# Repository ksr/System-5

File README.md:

# System-5 — a PCB-based 1802 ELF

System-5 is a printed-circuit-board 1802 computer built in 2004–2005 to run
Mike Riley's **ELF/OS**. It replaced the wire-wrapped System-4 (1979–1982) one
card at a time while keeping the System-4 30-pin bus, so old wire-wrap cards and
new PCB cards could be mixed. All the 2005 boards were designed in **Eagle 4.x**;
the boards of 2026 are **KiCad** designs.

Original write-up: the 2005 1802 website, no longer online; a copy is in `docs/website-2005/`.

The project's website is <https://system5.cottageworker.com>. This repository is public as
<https://github.com/ksr/System-5>, a copy made from Ken's working repository (`tools/public/README.md`).

## The system

| Card | Folder | Summary |
|---|---|---|
| Bus | `hardware/bus` | The 30-pin bus kept from System-4: Rev A 1982, Rev B Dec 2005 (dropped ±12V, added N1/N2); pinout in `hardware/board-notes/BoardNotes.txt`. **In the machine: the 2009 PCB backplane**, six 36-pin slots, no regulator, no pull-ups (System-4's backplane was Vero board). **Rev D** (S5BUS-D, 2026, `kicad/rev-d/`): eight 36-pin slots, power switch, fuse, pull-ups and pull-downs. Designed, not ordered. |
| CPU | `hardware/cpu` | CDP1802, clock, CM1232 power-on reset/auto-run, mode control (run/load/wait/reset), 4K EPROM, VMA reset-address remap, EF jumpers, aux connectors for the front panel and 1861 card. **In the machine: Rev A** (Jan 2005, reworked). Rev B/C are unbuilt fixes; `eagle/cpu1-prototype` = first unrouted cut with the 1861 on board. **Rev D** (2026, `kicad/rev-d/`): a new CPU card for the 36-pin bus, 2 MHz or an external clock, RESET/RUN switch, a flag that lets a loaded program run from RAM after a reset, with a RAM LED to show it (2026-11-21). Designed, not ordered. |
| Memory | `hardware/memory` | 2× 62256 RAM + 2× 27256 EPROM, every 4K block jumper-enabled. **In the machine: Rev E** (MEM3-E, `kicad/rev-e/`; JLCPCB, 4 layers, built 2026-10-31): the 2005 Rev C circuit with three fixes. Before it: Rev A (2004, the first card built) → B (2005; reworked, in the machine until 2026) → C, and a 2014 `rev-c-mill` variant for PCB milling. Rev D (2026) is scrap. `mem1`/`mem2` are earlier 6116-based designs. |
| IO: 1861 video + keyboard | `hardware/io-1861-keyboard` | CDP1861 video, CDP1852 input port, I/O decode (from Mike Riley's ELF). PS/2 keyboard → **PAK-VI** (AWC Electronics PS/2-to-ASCII) → **PIC16F84** (serial→parallel, `pic-ps2-firmware/keyboard.c`) → 1852. **In the machine: Rev A** (Jan 2005), for the keyboard; the 1861 has never been tested. |
| 6845 video | `hardware/video-6845` | 6845 alphanumeric video card based on **BYTE, May 1979**. Composite + Electrohome drive outputs. Rev A Feb 2005 (the first working card, later stripped; `eagle/rev-a/`). **In the machine: Rev B** (lower case, simplified clocking, Apr 2005): the 2005 Eagle source in `eagle/rev-b/` and the KiCad order master in `kicad/rev-b/`. **Rev B-Clean** (2026, `kicad/rev-b-clean/`): Rev B's circuit and copper without the DE-9 (composite only) and with the 6845's light-pen input tied to ground, every part drawn and the silkscreen redone. Designed, not ordered. **Rev B-Clean-Keyboard** (2026, `kicad/rev-b-clean-keyboard/`): Rev B-Clean with a PS/2 keyboard on the card (VIDEO-G TEXT's keyboard section: the key at 7802, the status at 7804), the 36-pin bus connector, and the video and keyboard jacks together at the front edge; it runs the VIDEO-G HBIOS. Designed, not ordered. |
| CF disk (IDE) | `hardware/ide-cf` | Mike Riley's 8-bit IDE interface plus port-select jumpers; used with a CF-to-IDE adapter and a 16MB CF card. **In the machine: Rev A** (Feb 2005). |
| Breadboard proto | `hardware/proto-breadboard` | Solderless-breadboard prototyping card. Drawn in 2005, never made. |
| Bus driver | `hardware/bus-driver` | New, 2026: Arduino Nano and 2× MCP23017 on the bus, a test card after the YACC1 bus tester. It runs bus cycles in place of the CPU, or steps and traces the CPU. **Rev B** (BUSDRV-B, `kicad/rev-b/`; JLCPCB, 2 layers) is built and working since 2026-10-30. Rev A is scrap: routed on 4 layers, ordered from a 2-layer zip. **Rev C** (BUSDRV-C, `kicad/rev-c/`, drawn 2026-11-18, not ordered): all 36 bus positions with a third MCP23017, LOAD mode by the clock, CLK OUT and probes on the Nano, a DEBUG header cabled to CPU Rev D's. The firmware has a **short finder** for either card since 2026-11-21: one bus line driven alone, every other watched (`python3 bringup.py shorts`, `software/busdrv/BRINGUP.md`); tried in the simulator only. |
| IO panel | `hardware/io-panel` | New, 2026: the front panel as a card on the 36-pin bus. 8 toggles, 8 LEDs, six TIL311 hex displays (the data byte and the bus address), Q LED, INPUT button, ELF-style RUN/LOAD, a real-time clock and, since 2026-11-20, a serial port (16C550, DE-9). Since 2026-11-22 a 50-pin header at its front edge for the front panel's ribbon (the card is 8.00 in long), and its DMA request put right: as first drawn it would have loaded every byte twice. Since 2026-11-23 its own RESET button, which boots the EPROM (the RUN/RESET toggle restarts what ran before), and the serial port's settings on the silkscreen. Since 2026-11-25 its DMA request and the toggles' drive start from a known state at power-up (D1, R5, R6; U23 a 74HCT03), and since 2026-11-26 its RESET button is at the far end of the front edge from INPUT. Rev A (`kicad/rev-a/`) designed, not ordered. No front panel was designed in 2005: the System-4 wire-wrap panel was used via the CPU card header. |
| Front panel | `hardware/front-panel` | New, 2026-11-22: a board that mounts as the front of a case, on a 50-way ribbon from the IO panel card. Six TIL311s (the bus address and the data byte), bit and status LEDs (PWR, Q, PAUSE, RESET, ROM, START FROM RAM), eight data toggles, RUN and LOAD, INPUT, and a RESET button that boots the EPROM (beside START FROM RAM since 2026-11-26, away from INPUT). Nothing goes to the CPU card: a boot reset is a state of the bus (`docs/manual/bus.md`). Rev A (`kicad/rev-a/`) designed, not ordered. |
| VIDEO-G | `hardware/video-g` | New, 2026: the next video card, two boards joined by a 40-pin ribbon. **TEXT**: 6845 text, 64 × 25 or 64 × 32, with a PS/2 keyboard. **GFX**: graphics, 512 × 200 or 512 × 256, with a PS/2 mouse. All memory-mapped in its own block, no I/O ports (2026-11-17). Version 1.0 (`kicad/`) designed, not ordered. |

The machine today (2026-11-14) is the 2009 backplane with CPU Rev A, memory Rev E, 6845 Rev B, IO Rev A and IDE Rev A. The five new boards (bus Rev D, CPU Rev D, the IO panel and the two VIDEO-G boards) pass the older check, `tools/preorder_check.py`, and none is ordered. Before an order each has to pass `pcb-check`, Ken's check for the boards of all his systems since 2026-11-06 (`hardware/BUILD-RULES.md`, section 2): all five have, as they are now: the bus Rev D on 2026-11-18, the other four on 2026-11-19, after their labels were moved out from under the bus connector (and VIDEO-G TEXT got the 36-pin connector); the IO panel again on 2026-11-20, with its serial port; CPU Rev D again on 2026-11-21, with its RAM LED. On 2026-11-22 CPU Rev D and the IO panel were changed and a sixth board, the front panel, was drawn (a boot reset on the bus; the IO panel's header and its DMA request): all three pass `pcb-check --tests` (last on 2026-11-23, at `26e17ea`: CPU Rev D and the front panel with no failures and no warnings, the IO panel with no failures and one warning, which Ken accepted that day: its DE-9 begins 65.6 mm from the front edge, where the check allows 60). They were drawn on the branch `front-panel` and are in `main` since 2026-11-23 (Ken: "merge everything"). Since then: VIDEO-G TEXT routed again with its 6845 write-only (2026-11-24; `pcb-check --tests` at `38fc4d0`, no failures, 0 warnings, GFX the same), the IO panel's power-up fix (2026-11-25), and both panels' RESET buttons moved away from INPUT (2026-11-26; `pcb-check --tests`: the front panel at `803c3a8`, no failures, 0 warnings; the IO panel at `6f4359d`, no failures, the accepted warning). None is ordered. `STATUS.md` has every board's state.

Board conventions (size 5.50" × 3.75", LED positions, labelling `KSR -- XXX#-A`,
CAM jobs) are in `hardware/board-notes/`.

Each board has an `eagle/<rev>/` tree (production gerbers in `fab/`) and, once converted, a `kicad/<rev>/` tree. Which boards were ordered: `hardware/FABRICATED.md`. Open work: `BACKLOG.md`. A summary of where everything stands (2026-11-14): `STATUS.md`.

Where both the Eagle working folder and the published website had a file with
the same name but different content, the website version is kept in a
`website-copy/` subfolder. Eagle's numbered backups (`*.b#1`, `*.s##`, …) are in
`eagle-backups/` subfolders.

## Firmware (Ken's)

- `firmware/hbios/` — **HBIOS**: 6845 video and keyboard drivers layered on Mike
  Riley's ELF/OS BIOS (changes marked `#define KSR`); boots into the BIOS's
  monitor, `minimon`, which is Mike's. `v1.0.6` is current, in the machine since 2026-11-15 (v1.0.4 plus the commands
  Ken added to that monitor, `H`, `B`, `D` and `Q1` / `Q0`, and the disk calls
  always in LBA mode, which Elf/OS v5 needs; built by its `build.py`); `v1.0.5`, `v1.0.4`, `v0.9` and `old/` are
  earlier builds. `v1.0.7` (2026-11-17, burned that day, not yet in the machine) adds `@F1E0`: the code of each key pressed, as `0x31`, on the
  bottom line of the screen, until Reset. `v1.0.8` (2026-11-18, emulator only) adds a driver for the IO panel's real-time
  clock (a DS12885 on ports 6/7) behind `f_gettod` / `f_settod`, and `f_getdev` bit 4. v1.0.4 builds with `rcasm` + `srec_cat` into a ROM
  at `0xF000`. `video-g/` is a build for the VIDEO-G card (everything
  memory-mapped: the 6845 at 7800/7801, the key at 7802; 64 x 25, a faster scroll; for the emulator, not burned).
  Mike Riley's BIOS comes under his notice (`firmware/hbios/NOTICE.md`: free to use and share with the notice kept,
  not for commercial use without his permission).
- `firmware/rom-tests/` — test ROM (`sec2`).
- `firmware/char-rom-fonts/` — 2513 character-generator ROM images and C tools
  to build/view font EPROMs for the 6845 card.

## Software (Ken's host tools)

- `software/s5emu/` — System-5 emulator and debugger (terminal + browser; in a browser tab on a Mac or in a GitHub Codespace: `software/s5emu/CODESPACE.md`, `.devcontainer/`): runs the real HBIOS ROM and boots ELF/OS from a disk image; 1861, IDE/CF, 6845, keyboard, memory jumpers, bus-driver link; `--video g` models the VIDEO-G card.

- `software/gbasic/` — **GBASIC**, an integer BASIC for ELF/OS with VIDEO-G graphics (1802 assembly, 2026-11-01): the source, the built program, its language reference (`README.md`) and tests in the emulator.

- `tools/render_populated.py` — a KiCad render of a board with its parts drawn in, for the website's pictures (the board file is only read)
- `tools/asm1802.py` — a Python 1802 assembler (rcasm syntax, short-branch page check, relaxing jumps, macros); builds GBASIC and the VIDEO-G HBIOS.

- `software/busdrv/` — `s5busdrv.py`, the host tool for the bus driver card (peek/poke/dump, hex load with verify, memtest, I/O, bus watch); firmware in `embedded/bus-driver/`.

- `software/elfos-v5/` — System-5 programs for Mike Riley's Elf/OS v5 (`cls`) and `v5card.py`, which reads and
  changes a v5 card image (`ls`, `get`, `put`, `add`).

## Kept private (third-party)

Other people's work that System-5 is built with, and that carries no permission to publish it, is not in this
repository. Since 2026-11-15 it is in Ken's private repository `private-resources` (`github.com/ksr/private-resources`),
which sits beside this one, so the paths below are written `../private-resources/elf/...`; each keeps the path it had
here.

- `reference/mike-riley/` — **ELF/OS** (kernel 135, utilities and languages,
  0.2.6 release; Elf/OS v5 and its System-5 card image), **rcasm** 2007 source, **EDTASM**, MicroElf/PicoElf boards
  and a mirror of elf-emulation.com.
- `reference/elf2000-spare-time-gizmos/` — **ELF2000** (Spare Time Gizmos /
  Bob Armstrong): manuals, EELF, ELF-Disk, STG1861, ROM v60/v87 images (with
  Ken's EPROM-split Makefiles), ElfOS-2K 0.2.8. Not part of System-5.
- `reference/tiny-basic/` — Lee Hart/TMSI 1802 Tiny BASIC; RCA Tiny BASIC (Herb Johnson).
- `reference/tools/` — A18 assembler, TASM 3.1, 1806 disassembler, srecord
  source tarballs (1.20/1.23/1.27), Macro Assembler AS manual, LCD font tool.
- `reference/datasheets/` — CDP1802 datasheet, RCA MPM-201A 1802 User Manual (1976), EPROM databook.
- `firmware/elfos-install-rom/` — the ELF/OS install image for the memory card's EPROM, and the read of the one in
  MEM3-E's IC5 (`hardware/memory/eagle/rev-b/bringup/*.bin`).
- `firmware/system4-tiny-basic-rom/` — the Tiny BASIC EPROM pulled from the System-4 wire-wrap machine, and its
  disassembly.
- `software/disktool/` — Mike Riley's 2005 disktool, which builds and writes ELF/OS disks (with `kernel.bin`).
- `software/rcasm-mac-build/` — rcasm source patched in 2017 to build on macOS (with a Mac x86_64 binary).

Without them the emulator still runs HBIOS (whose BIOS part Mike Riley allows to be shared, above), but has no ELF/OS
disk to boot, and the tests that need one are skipped.

## Licence

Ken's designs and documents are CC BY 4.0, his software MIT; HBIOS's BIOS part, the 2513 fonts and some library parts
are other people's: [`LICENSE.md`](LICENSE.md).

## Docs

- `docs/website-2005/` — "Ken's 1802 World" site (System-1, System-4, System-5,
  stand-alone projects, photos). Files that are also elsewhere in this repo
  (schematics, BIOS source, tool tarballs) were removed here (the list is
  `docs/.removed-dups.txt`, kept with Ken's working notes).
- `docs/website-older/` — earlier versions of the same site.

The visitor counter the Yahoo host added to 33 of the old pages was taken out on 2026-11-15; nothing else in them was
changed.

## Other projects

1802 work that is not System-5 (the Netronics ELF II recreation, the 2020 COSMAC ELF PCB, the ELF2000/PicoElf
ROMs, the ET-3400 EPROM reads and general 1802 documentation) is in a separate private repository since 2026-10-26,
split out of this one with its history.

## Provenance

Assembled 2026-10-04 from `~/Documents/Projects/elf-1`, `elf-2` and `1802`
(all left untouched). `elf-1` was largely a subset of `elf-2`; exact duplicates were
collapsed to one copy. Not carried over: FrontPage `_vti_*` metadata, vim swap
files, `.o` objects, extracted srecord build trees (source tarballs kept), and
2005-era Linux i386 binaries that have source alongside. Duplicate include
files inside individual ELF/OS program folders were left in place because each
program's build expects them.

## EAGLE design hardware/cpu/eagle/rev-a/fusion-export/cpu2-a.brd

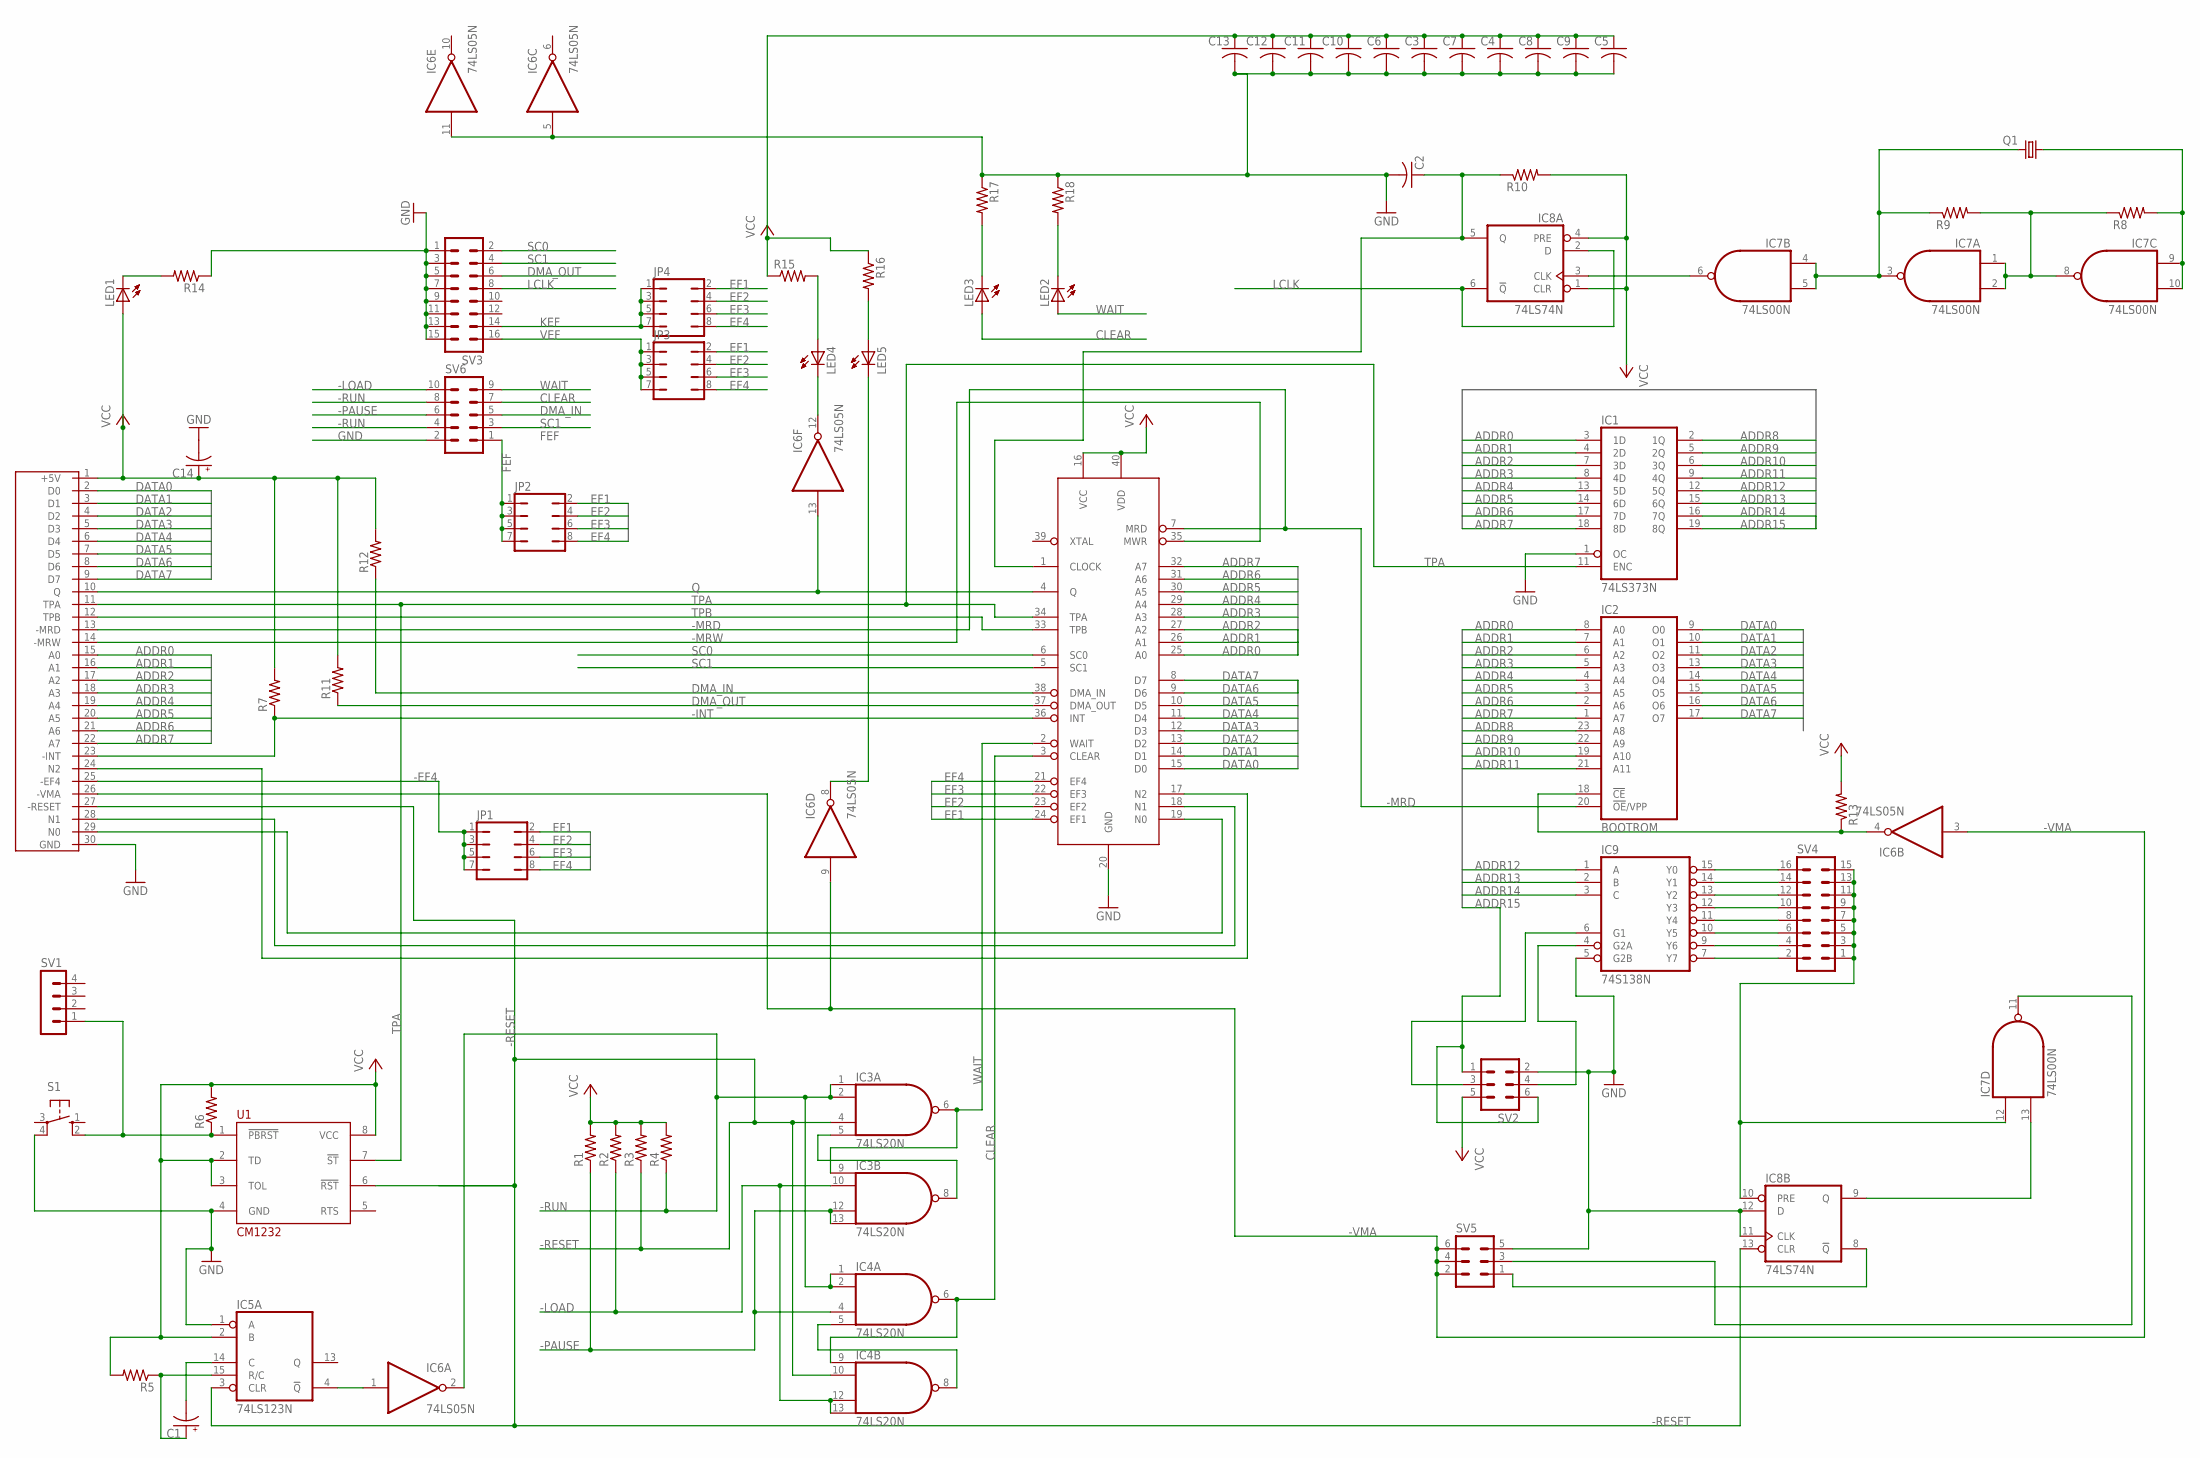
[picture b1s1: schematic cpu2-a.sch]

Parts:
C1, C14: CPOL-USE2.5-7; E2,5-7
C2: C-US025-025X050; C025-025X050
C3, C4, C5, C6, C7, C8, C9, C10, C11, C12, C13: C-US025-050X050; C025-050X050
IC1: 74LS373N; DIL20
IC2: BOOTROM; DIL24
IC3, IC4: 74LS20N; DIL14
IC5: 74LS123N; DIL16
IC6: 74LS05N; DIL14
IC7: 74LS00N; DIL14
IC8: 74LS74N; DIL14
IC9: 74S138N; DIL16
JP1, JP2, JP3, JP4: JP4Q
LED1, LED2, LED3, LED4, LED5: LED5MM
Q1: CRYTALHC49U70; HC49U70
R1, R2, R3, R4, R5, R6, R7, R8, R9, R10, R11, R12, R13: R-US_0207/2V; 0207/2V
R14, R15, R16, R17, R18: R-US_0207/7; 0207/7
S1: 10-XX; B3F-10XX
SV1: MA04-1
SV2, SV5: MA03-2
SV3, SV4: MA08-2
SV6: MA05-2
U1: CM1232; DIP-8
U$1: CDP1802BCECDP1802BCE; DIL40
U$2: C30

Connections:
-EF4: JP1.1, JP1.3, JP1.5, JP1.7, U$2.25 (-EF4)
-INT: R7.1, U$1.36 (INT), U$2.23 (-INT)
-LOAD: IC3.10 (I1), IC4.12 (I2), IC4.13 (I3), R2.1, SV6.10
-MRD: IC2.20 (!OE!/VPP), U$1.7 (MRD), U$2.13 (-MRD)
-MRW: U$1.35 (MWR), U$2.14 (-MRW)
-PAUSE: IC3.12 (I2), IC3.13 (I3), IC4.4 (I2), R1.1, SV6.6
-RESET: IC3.4 (I2), IC4.10 (I1), IC5.3 (CLR), IC8.13 (CLR), R3.1, U1.6 (!RST), U$2.27 (-RESET)
-RUN: IC3.1 (I0), IC3.2 (I1), IC4.1 (I0), IC4.2 (I1), IC6.2 (O), R4.1, SV6.4, SV6.8
-VMA: IC6.3 (I), IC6.9 (I), SV5.2, SV5.4, SV5.6, U$2.26 (-VMA)
ADDR0: IC1.3 (1D), IC2.8 (A0), U$1.25 (A0), U$2.15 (A0)
ADDR1: IC1.4 (2D), IC2.7 (A1), U$1.26 (A1), U$2.16 (A1)
ADDR2: IC1.7 (3D), IC2.6 (A2), U$1.27 (A2), U$2.17 (A2)
ADDR3: IC1.8 (4D), IC2.5 (A3), U$1.28 (A3), U$2.18 (A3)
ADDR4: IC1.13 (5D), IC2.4 (A4), U$1.29 (A4), U$2.19 (A4)
ADDR5: IC1.14 (6D), IC2.3 (A5), U$1.30 (A5), U$2.20 (A5)
ADDR6: IC1.17 (7D), IC2.2 (A6), U$1.31 (A6), U$2.21 (A6)
ADDR7: IC1.18 (8D), IC2.1 (A7), U$1.32 (A7), U$2.22 (A7)
ADDR8: IC1.2 (1Q), IC2.23 (A8)
ADDR9: IC1.5 (2Q), IC2.22 (A9)
ADDR10: IC1.6 (3Q), IC2.19 (A10)
ADDR11: IC1.9 (4Q), IC2.21 (A11)
ADDR12: IC1.12 (5Q), IC9.1 (A)
ADDR13: IC1.15 (6Q), IC9.2 (B)
ADDR14: IC1.16 (7Q), IC9.3 (C)
ADDR15: IC1.19 (8Q), SV2.1, SV2.6
CLEAR: IC4.6 (O), IC4.9 (I0), LED3.A, SV6.7, U$1.3 (CLEAR)
DATA0: IC2.9 (O0), U$1.15 (D0), U$2.2 (D0)
DATA1: IC2.10 (O1), U$1.14 (D1), U$2.3 (D1)
DATA2: IC2.11 (O2), U$1.13 (D2), U$2.4 (D2)
DATA3: IC2.13 (O3), U$1.12 (D3), U$2.5 (D3)
DATA4: IC2.14 (O4), U$1.11 (D4), U$2.6 (D4)
DATA5: IC2.15 (O5), U$1.10 (D5), U$2.7 (D5)
DATA6: IC2.16 (O6), U$1.9 (D6), U$2.8 (D6)
DATA7: IC2.17 (O7), U$1.8 (D7), U$2.9 (D7)
DMA_IN: R12.1, SV6.5, U$1.38 (DMA_IN)
DMA_OUT: R11.1, SV3.6, U$1.37 (DMA_OUT)
EF1: JP1.2, JP2.2, JP3.2, JP4.2, U$1.24 (EF1)
EF2: JP1.4, JP2.4, JP3.4, JP4.4, U$1.23 (EF2)
EF3: JP1.6, JP2.6, JP3.6, JP4.6, U$1.22 (EF3)
EF4: JP1.8, JP2.8, JP3.8, JP4.8, U$1.21 (EF4)
FEF: JP2.1, JP2.3, JP2.5, JP2.7, SV6.1
GND: C2.2, C3.2, C4.2, C5.2, C6.2, C7.2, C8.2, C9.2, C10.2, C11.2, C12.2, C13.2, C14.-, IC1.1 (OC), IC1.10 (GND), IC2.12 (GND), IC3.7 (GND), IC4.7 (GND), IC5.1 (A), IC5.8 (GND), IC6.5 (I), IC6.7 (GND), IC6.11 (I), IC7.7 (GND), IC8.7 (GND), IC8.11 (CLK), IC8.12 (D), IC9.5 (G2B), IC9.8 (GND), R14.1, R17.1, R18.1, S1.4 (P1), SV2.2, SV3.1, SV3.3, SV3.5, SV3.7, SV3.9, SV3.11, SV3.13, SV3.15, SV5.5, SV6.2, U1.4 (GND), U$1.20 (GND), U$2.30 (GND)
KEF: JP4.1, JP4.3, JP4.5, JP4.7, SV3.14
LCLK: IC8.2 (D), IC8.6 (!Q), SV3.8
N0: U$1.19 (N0), U$2.29 (N0)
N1: U$1.18 (N1), U$2.28 (N1)
N2: U$1.17 (N2), U$2.24 (N2)
unnamed: IC7.11 (O), SV5.3
unnamed: R6.1, S1.2 (S1), SV1.1, U1.1 (!PBRST)
unnamed: IC2.18 (!CE), IC6.4 (O), R13.1
unnamed: IC7.13 (I1), IC8.9 (Q)
unnamed: LED1.K (C), R14.2
unnamed: IC8.8 (!Q), SV5.1
unnamed: IC6.12 (O), LED4.K (C)
unnamed: LED4.A, R15.2
unnamed: LED3.K (C), R17.2
unnamed: LED2.K (C), R18.2
unnamed: LED5.A, R16.2
unnamed: IC5.4 (!Q), IC6.1 (I)
unnamed: IC7.1 (I0), IC7.2 (I1), IC7.8 (O), R8.1, R9.2
unnamed: C1.+, IC5.15 (R/C), R5.1
unnamed: IC7.3 (O), IC7.4 (I0), IC7.5 (I1), Q1.2, R9.1
unnamed: C1.-, IC5.14 (C)
unnamed: IC9.4 (G2A), SV2.4
unnamed: IC7.9 (I0), IC7.10 (I1), Q1.1, R8.2
unnamed: IC3.5 (I3), IC3.8 (O)
unnamed: IC7.6 (O), IC8.3 (CLK)
unnamed: IC4.5 (I3), IC4.8 (O)
unnamed: IC6.8 (O), LED5.K (C)
unnamed: C2.1, IC8.5 (Q), R10.1, U$1.1 (CLOCK)
unnamed: IC9.15 (Y0), SV4.16
unnamed: IC9.14 (Y1), SV4.14
unnamed: IC9.13 (Y2), SV4.12
unnamed: IC9.12 (Y3), SV4.10
unnamed: IC9.11 (Y4), SV4.8
unnamed: IC9.10 (Y5), SV4.6
unnamed: IC9.9 (Y6), SV4.4
unnamed: IC9.7 (Y7), SV4.2
unnamed: IC7.12 (I0), IC8.10 (PRE), SV4.1, SV4.3, SV4.5, SV4.7, SV4.9, SV4.11, SV4.13, SV4.15
unnamed: IC9.6 (G1), SV2.3
Q: IC6.13 (I), U$1.4 (Q), U$2.10 (Q)
SC0: SV3.2, U$1.6 (SC0)
SC1: SV3.4, SV6.3, U$1.5 (SC1)
TPA: IC1.11 (ENC), U1.7 (!ST), U$1.34 (TPA), U$2.11 (TPA)
TPB: U$1.33 (TPB), U$2.12 (TPB)
VCC: C3.1, C4.1, C5.1, C6.1, C7.1, C8.1, C9.1, C10.1, C11.1, C12.1, C13.1, C14.+, IC1.20 (VCC), IC2.24 (VCC), IC3.14 (VCC), IC4.14 (VCC), IC5.2 (B), IC5.16 (VCC), IC6.14 (VCC), IC7.14 (VCC), IC8.1 (CLR), IC8.4 (PRE), IC8.14 (VCC), IC9.16 (VCC), LED1.A, R1.2, R2.2, R3.2, R4.2, R5.2, R6.2, R7.2, R10.2, R11.2, R12.2, R13.2, R15.1, R16.1, SV2.5, U1.2 (TD), U1.3 (TOL), U1.8 (VCC), U$1.16 (VCC), U$1.40 (VDD), U$2.1 (+5V)
VEF: JP3.1, JP3.3, JP3.5, JP3.7, SV3.16
WAIT: IC3.6 (O), IC3.9 (I0), LED2.A, SV6.9, U$1.2 (WAIT)

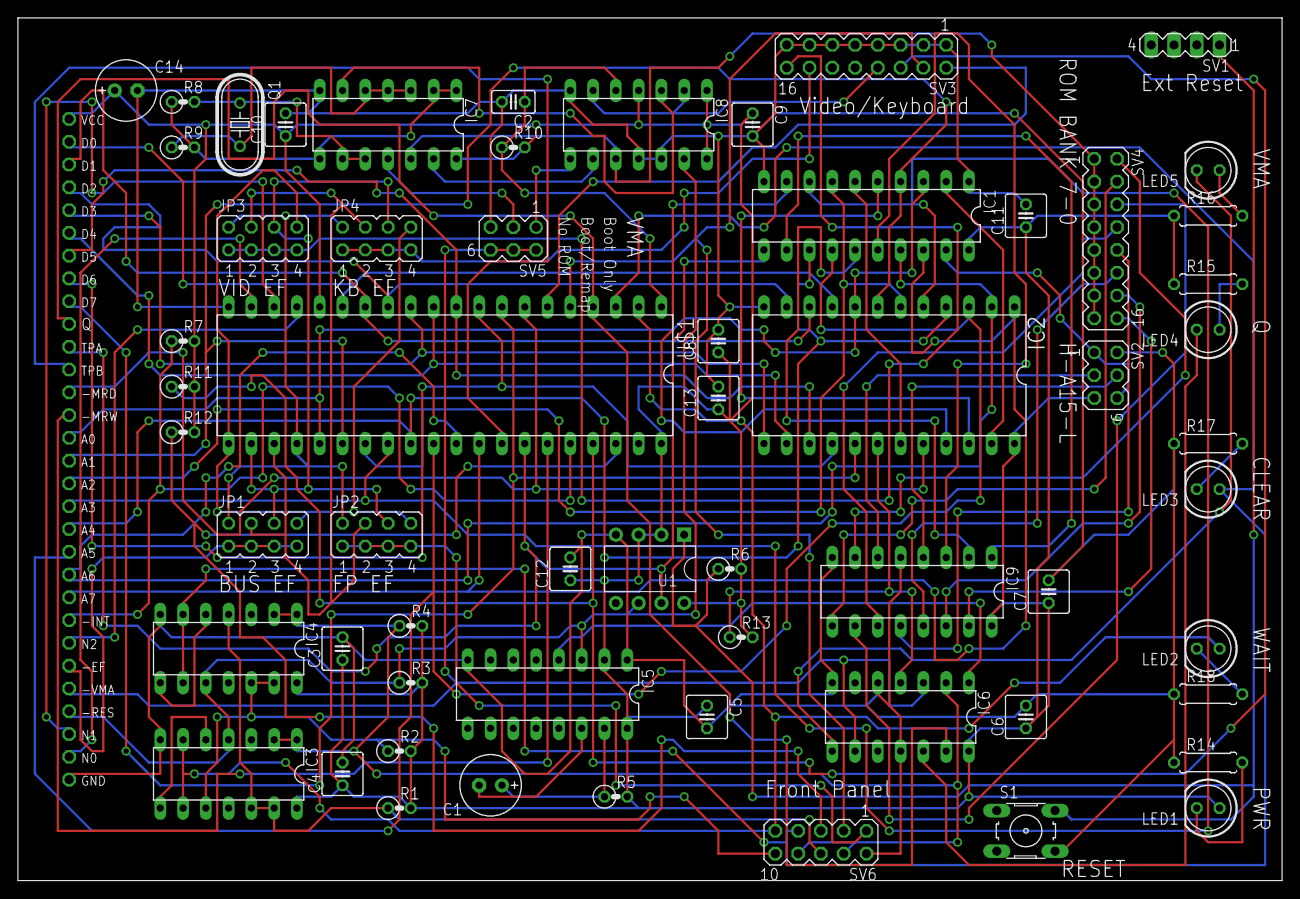
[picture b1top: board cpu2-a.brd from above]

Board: 2 copper layers, 140.9 x 96.2 mm, 61 parts (0 on the bottom side), 88 nets.

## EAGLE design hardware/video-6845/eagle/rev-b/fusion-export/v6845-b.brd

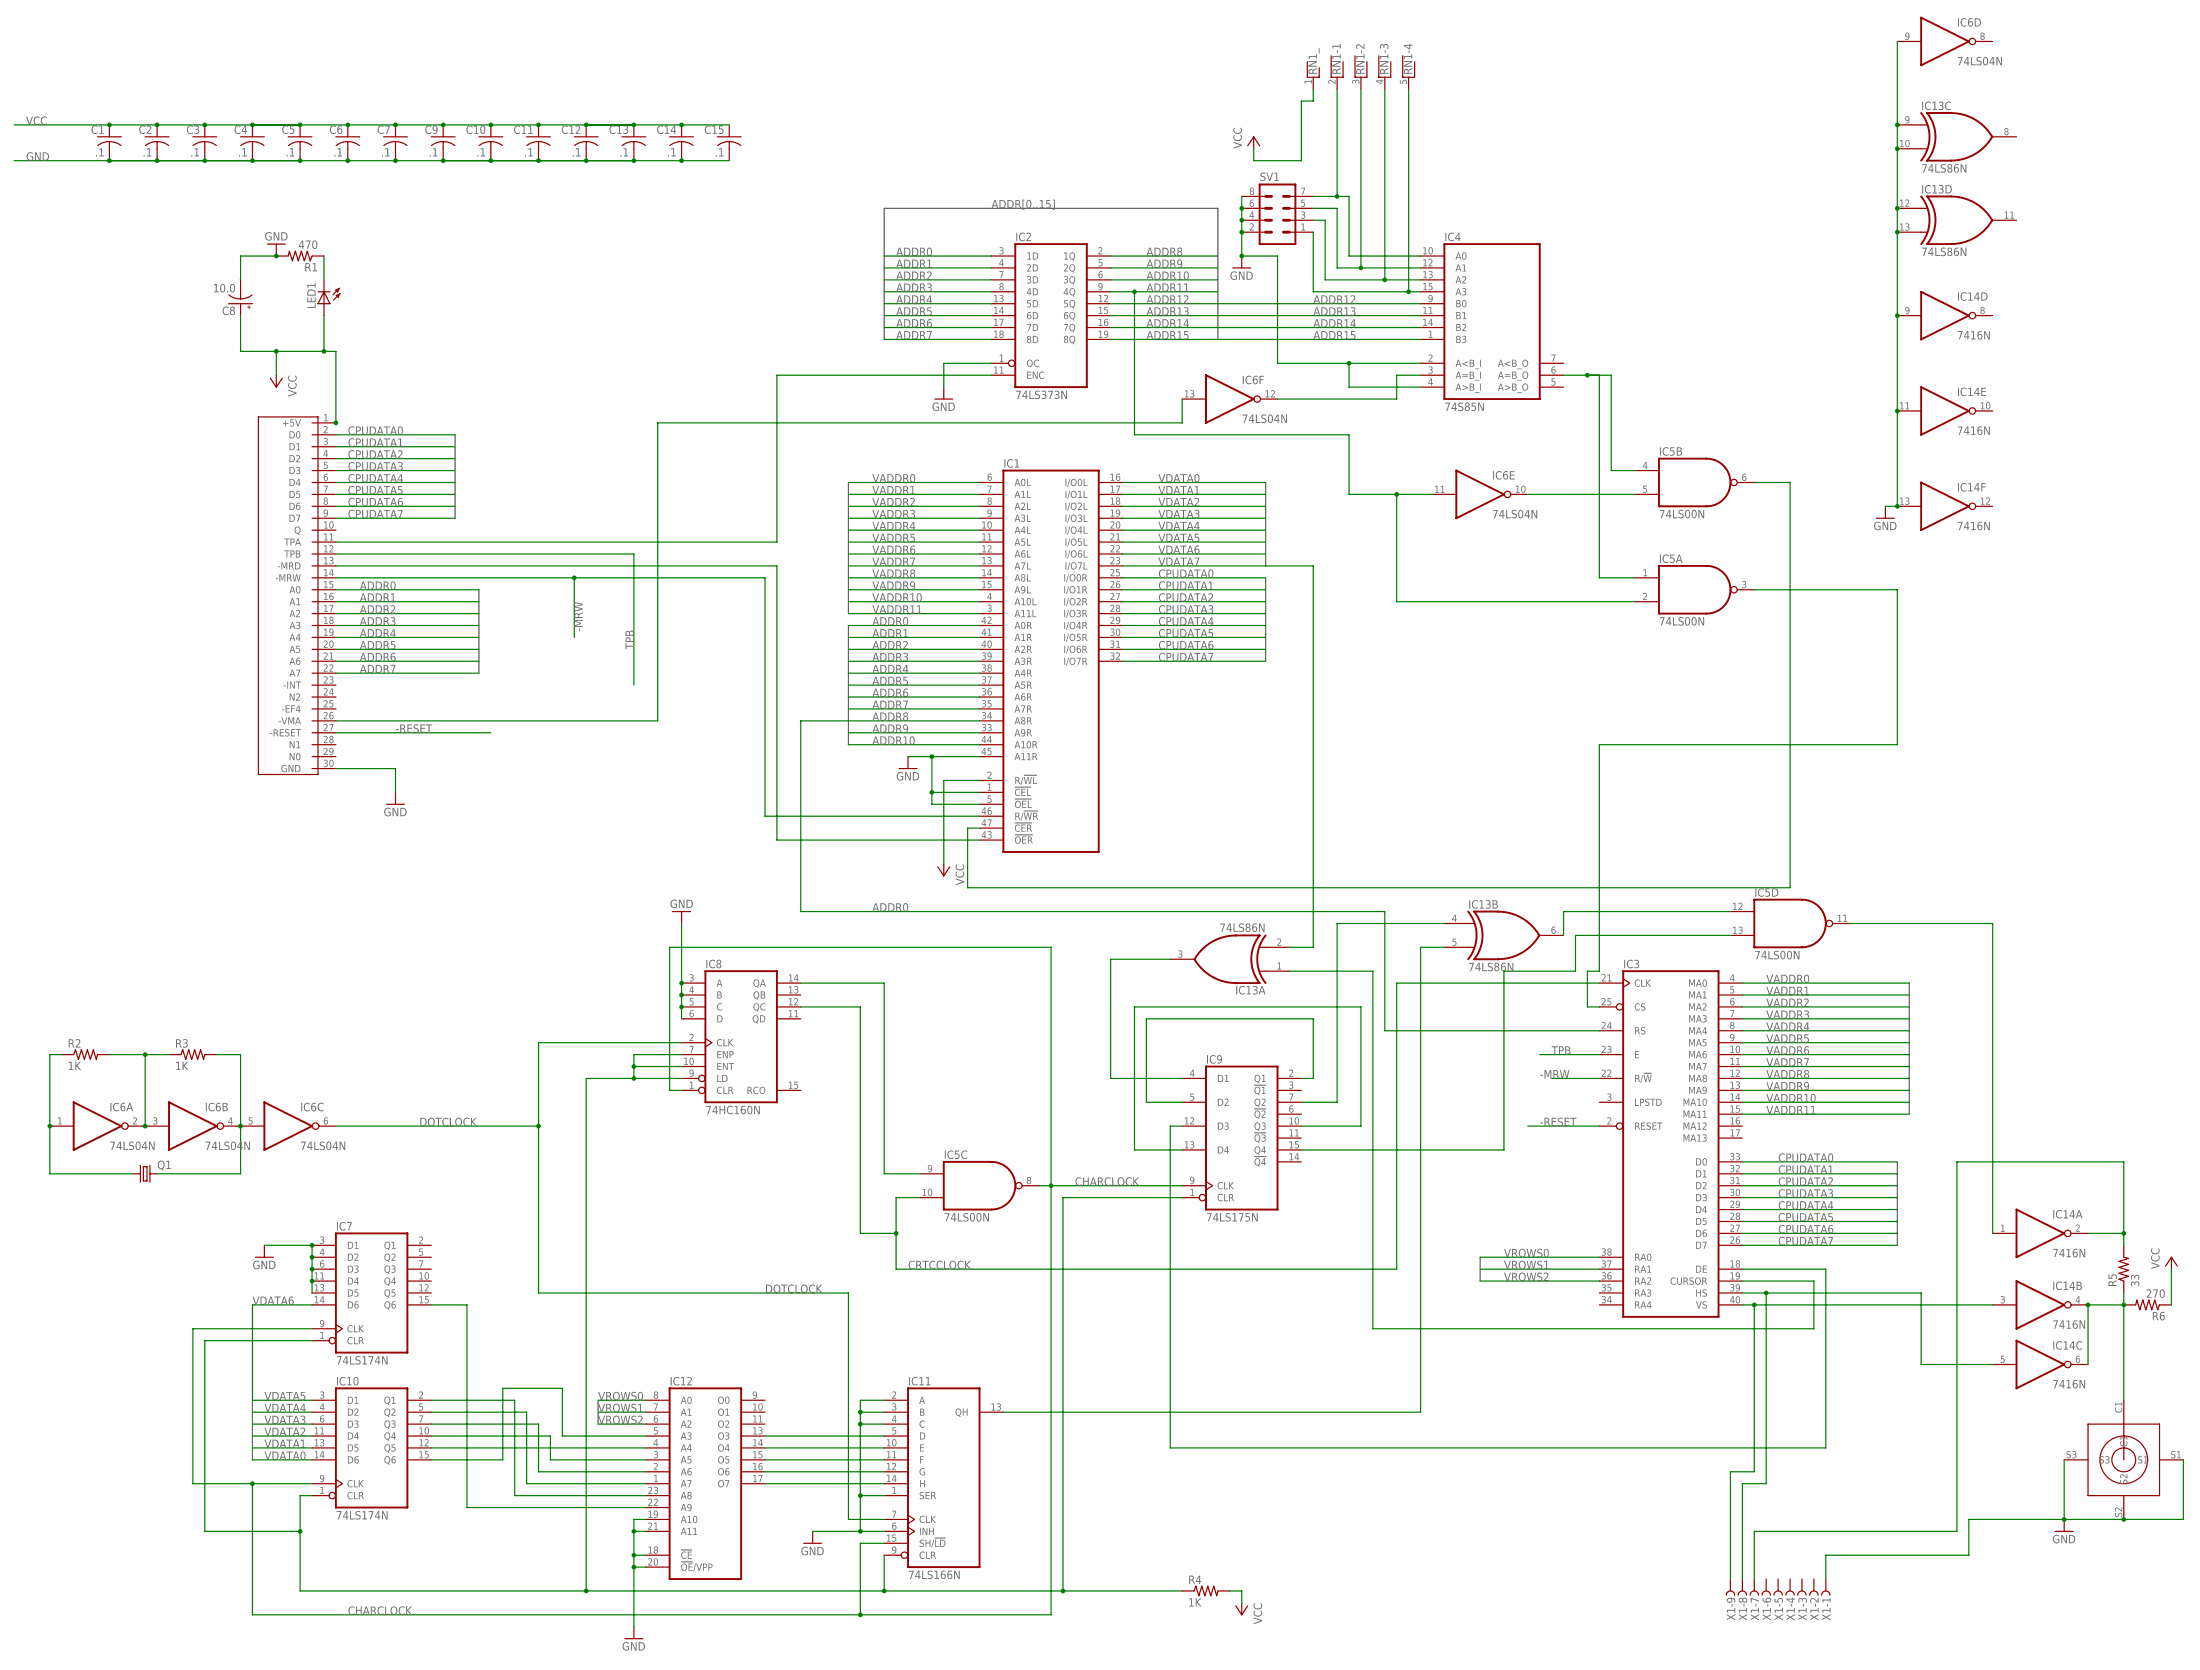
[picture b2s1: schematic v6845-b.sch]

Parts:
C1, C2, C3, C4, C5, C6, C7, C9, C10, C11, C12, C13, C14, C15: .1; C025-050X050
C8: 10.0; E2,5-7
IC1: 7134P; DIL48
IC2: 74LS373N; DIL20
IC3: 6845; DIL40
IC4: 74S85N; DIL16
IC5: 74LS00N; DIL14
IC6: 74LS04N; DIL14
IC7, IC10: 74LS174N; DIL16
IC8: 74HC160N; DIL16
IC9: 74LS175N; DIL16
IC11: 74LS166N; DIL16
IC12: 2732; DIL24
IC13: 74LS86N; DIL14
IC14: 7416N; DIL14
LED1: LED5MM
Q1: CRYTALHC49U-V; HC49U-V
R1: 470; 0207/7
R2, R3, R4: 1K; 0207/7
R5: 33; 0207/7
R6: 270; 0207/7
RN1: RNX4; RN-5
SV1: MA04-2
U$1: C30
U$4: RCA
X1: F09HPS; F09HP

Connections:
-MRW: IC1.46 (R/!WR), IC3.22 (R/!W), U$1.14 (-MRW)
-RESET: IC3.2 (RESET), U$1.27 (-RESET)
ADDR0: IC1.42 (A0R), IC2.3 (1D), IC3.24 (RS), U$1.15 (A0)
ADDR1: IC1.41 (A1R), IC2.4 (2D), U$1.16 (A1)
ADDR2: IC1.40 (A2R), IC2.7 (3D), U$1.17 (A2)
ADDR3: IC1.39 (A3R), IC2.8 (4D), U$1.18 (A3)
ADDR4: IC1.38 (A4R), IC2.13 (5D), U$1.19 (A4)
ADDR5: IC1.37 (A5R), IC2.14 (6D), U$1.20 (A5)
ADDR6: IC1.36 (A6R), IC2.17 (7D), U$1.21 (A6)
ADDR7: IC1.35 (A7R), IC2.18 (8D), U$1.22 (A7)
ADDR8: IC1.34 (A8R), IC2.2 (1Q)
ADDR9: IC1.33 (A9R), IC2.5 (2Q)
ADDR10: IC1.44 (A10R), IC2.6 (3Q)
ADDR11: IC2.9 (4Q), IC5.2 (I1), IC6.11 (I)
ADDR12: IC2.12 (5Q), IC4.9 (B0)
ADDR13: IC2.15 (6Q), IC4.11 (B1)
ADDR14: IC2.16 (7Q), IC4.14 (B2)
ADDR15: IC2.19 (8Q), IC4.1 (B3)
CHARCLOCK: IC5.8 (O), IC7.9 (CLK), IC8.1 (CLR), IC9.9 (CLK), IC10.9 (CLK), IC11.15 (SH/!LD)
CPUDATA0: IC1.25 (I/O0R), IC3.33 (D0), U$1.2 (D0)
CPUDATA1: IC1.26 (I/O1R), IC3.32 (D1), U$1.3 (D1)
CPUDATA2: IC1.27 (I/O2R), IC3.31 (D2), U$1.4 (D2)
CPUDATA3: IC1.28 (I/O3R), IC3.30 (D3), U$1.5 (D3)
CPUDATA4: IC1.29 (I/O4R), IC3.29 (D4), U$1.6 (D4)
CPUDATA5: IC1.30 (I/O5R), IC3.28 (D5), U$1.7 (D5)
CPUDATA6: IC1.31 (I/O6R), IC3.27 (D6), U$1.8 (D6)
CPUDATA7: IC1.32 (I/O7R), IC3.26 (D7), U$1.9 (D7)
CRTCCLOCK: IC3.21 (CLK), IC5.10 (I1), IC8.12 (QC)
DOTCLOCK: IC6.6 (O), IC8.2 (CLK), IC11.7 (CLK)
GND: C1.2, C2.2, C3.2, C4.2, C5.2, C6.2, C7.2, C8.-, C9.2, C10.2, C11.2, C12.2, C13.2, C14.2, C15.2, IC1.1 (!CEL), IC1.5 (!OEL), IC1.24 (GND), IC1.45 (A11R), IC2.1 (OC), IC2.10 (GND), IC3.1 (GND), IC4.2 (A<B_I), IC4.4 (A>B_I), IC4.8 (GND), IC5.7 (GND), IC6.7 (GND), IC6.9 (I), IC7.3 (D1), IC7.4 (D2), IC7.6 (D3), IC7.8 (GND), IC7.11 (D4), IC7.13 (D5), IC8.3 (A), IC8.4 (B), IC8.5 (C), IC8.6 (D), IC8.8 (GND), IC9.8 (GND), IC10.8 (GND), IC11.1 (SER), IC11.2 (A), IC11.3 (B), IC11.4 (C), IC11.6 (INH), IC11.8 (GND), IC12.12 (GND), IC12.18 (!CE), IC12.19 (A10), IC12.20 (!OE!/VPP), IC12.21 (A11), IC13.7 (GND), IC13.9 (I0), IC13.10 (I1), IC13.12 (I0), IC13.13 (I1), IC14.7 (GND), IC14.9 (I), IC14.11 (I), IC14.13 (I), R1.2, SV1.2, SV1.4, SV1.6, SV1.8, U$1.30 (GND), U$4.S1, U$4.S2, U$4.S3, X1.1
unnamed: IC1.43 (!OER), U$1.13 (-MRD)
unnamed: IC5.5 (I1), IC6.10 (O)
unnamed: IC3.25 (CS), IC5.3 (O)
unnamed: IC4.10 (A0), RN1.2, SV1.7
unnamed: IC4.12 (A1), RN1.3, SV1.5
unnamed: IC4.13 (A2), RN1.4, SV1.3
unnamed: IC4.15 (A3), RN1.5, SV1.1
unnamed: IC4.3 (A=B_I), IC6.12 (O)
unnamed: IC1.47 (!CER), IC5.6 (O)
unnamed: IC7.1 (CLR), IC8.7 (ENP), IC8.9 (LD), IC8.10 (ENT), IC9.1 (CLR), IC10.1 (CLR), IC11.9 (CLR), R4.1
unnamed: IC6.4 (O), IC6.5 (I), Q1.2, R3.2
unnamed: IC6.1 (I), Q1.1, R2.1
unnamed: IC7.15 (Q6), IC12.22 (A9)
unnamed: IC6.2 (O), IC6.3 (I), R2.2, R3.1
unnamed: IC3.19 (CURSOR), IC13.1 (I0)
unnamed: IC5.9 (I0), IC8.14 (QA)
unnamed: IC9.4 (D1), IC13.3 (O)
unnamed: LED1.K (C), R1.1
unnamed: IC9.2 (Q1), IC9.5 (D2)
unnamed: IC11.5 (D), IC12.13 (O3)
unnamed: IC11.10 (E), IC12.14 (O4)
unnamed: IC11.11 (F), IC12.15 (O5)
unnamed: IC11.12 (G), IC12.16 (O6)
unnamed: IC11.14 (H), IC12.17 (O7)
unnamed: IC10.2 (Q1), IC12.23 (A8)
unnamed: IC10.5 (Q2), IC12.1 (A7)
unnamed: IC10.7 (Q3), IC12.2 (A6)
unnamed: IC10.10 (Q4), IC12.3 (A5)
unnamed: IC10.12 (Q5), IC12.4 (A4)
unnamed: IC10.15 (Q6), IC12.5 (A3)
unnamed: IC9.7 (Q2), IC13.4 (I0)
unnamed: IC11.13 (QH), IC13.5 (I1)
unnamed: IC9.10 (Q3), IC9.13 (D4)
unnamed: IC3.18 (DE), IC9.12 (D3)
unnamed: IC5.12 (I0), IC13.6 (O)
unnamed: IC5.13 (I1), IC9.15 (Q4)
unnamed: IC3.40 (VS), IC14.3 (I), X1.9
unnamed: IC3.39 (HS), IC14.5 (I), X1.8
unnamed: IC5.11 (O), IC14.1 (I)
unnamed: IC14.4 (O), IC14.6 (O), R5.1, R6.2, U$4.C1
unnamed: IC14.2 (O), R5.2, X1.7
unnamed: IC4.6 (A=B_O), IC5.1 (I0), IC5.4 (I0)
unnamed: IC6.13 (I), U$1.26 (-VMA)
TPA: IC2.11 (ENC), U$1.11 (TPA)
TPB: IC3.23 (E), U$1.12 (TPB)
VADDR0: IC1.6 (A0L), IC3.4 (MA0)
VADDR1: IC1.7 (A1L), IC3.5 (MA1)
VADDR2: IC1.8 (A2L), IC3.6 (MA2)
VADDR3: IC1.9 (A3L), IC3.7 (MA3)
VADDR4: IC1.10 (A4L), IC3.8 (MA4)
VADDR5: IC1.11 (A5L), IC3.9 (MA5)
VADDR6: IC1.12 (A6L), IC3.10 (MA6)
VADDR7: IC1.13 (A7L), IC3.11 (MA7)
VADDR8: IC1.14 (A8L), IC3.12 (MA8)
VADDR9: IC1.15 (A9L), IC3.13 (MA9)
VADDR10: IC1.4 (A10L), IC3.14 (MA10)
VADDR11: IC1.3 (A11L), IC3.15 (MA11)
VCC: C1.1, C2.1, C3.1, C4.1, C5.1, C6.1, C7.1, C8.+, C9.1, C10.1, C11.1, C12.1, C13.1, C14.1, C15.1, IC1.2 (R/!WL), IC1.48 (VCC), IC2.20 (VCC), IC3.20 (VCC), IC4.16 (VCC), IC5.14 (VCC), IC6.14 (VCC), IC7.16 (VCC), IC8.16 (VCC), IC9.16 (VCC), IC10.16 (VCC), IC11.16 (VCC), IC12.24 (VCC), IC13.14 (VCC), IC14.14 (VCC), LED1.A, R4.2, R6.1, RN1.1, U$1.1 (+5V)
VDATA0: IC1.16 (I/O0L), IC10.14 (D6)
VDATA1: IC1.17 (I/O1L), IC10.13 (D5)
VDATA2: IC1.18 (I/O2L), IC10.11 (D4)
VDATA3: IC1.19 (I/O3L), IC10.6 (D3)
VDATA4: IC1.20 (I/O4L), IC10.4 (D2)
VDATA5: IC1.21 (I/O5L), IC10.3 (D1)
VDATA6: IC1.22 (I/O6L), IC7.14 (D6)
VDATA7: IC1.23 (I/O7L), IC13.2 (I1)
VROWS0: IC3.38 (RA0), IC12.8 (A0)
VROWS1: IC3.37 (RA1), IC12.7 (A1)
VROWS2: IC3.36 (RA2), IC12.6 (A2)

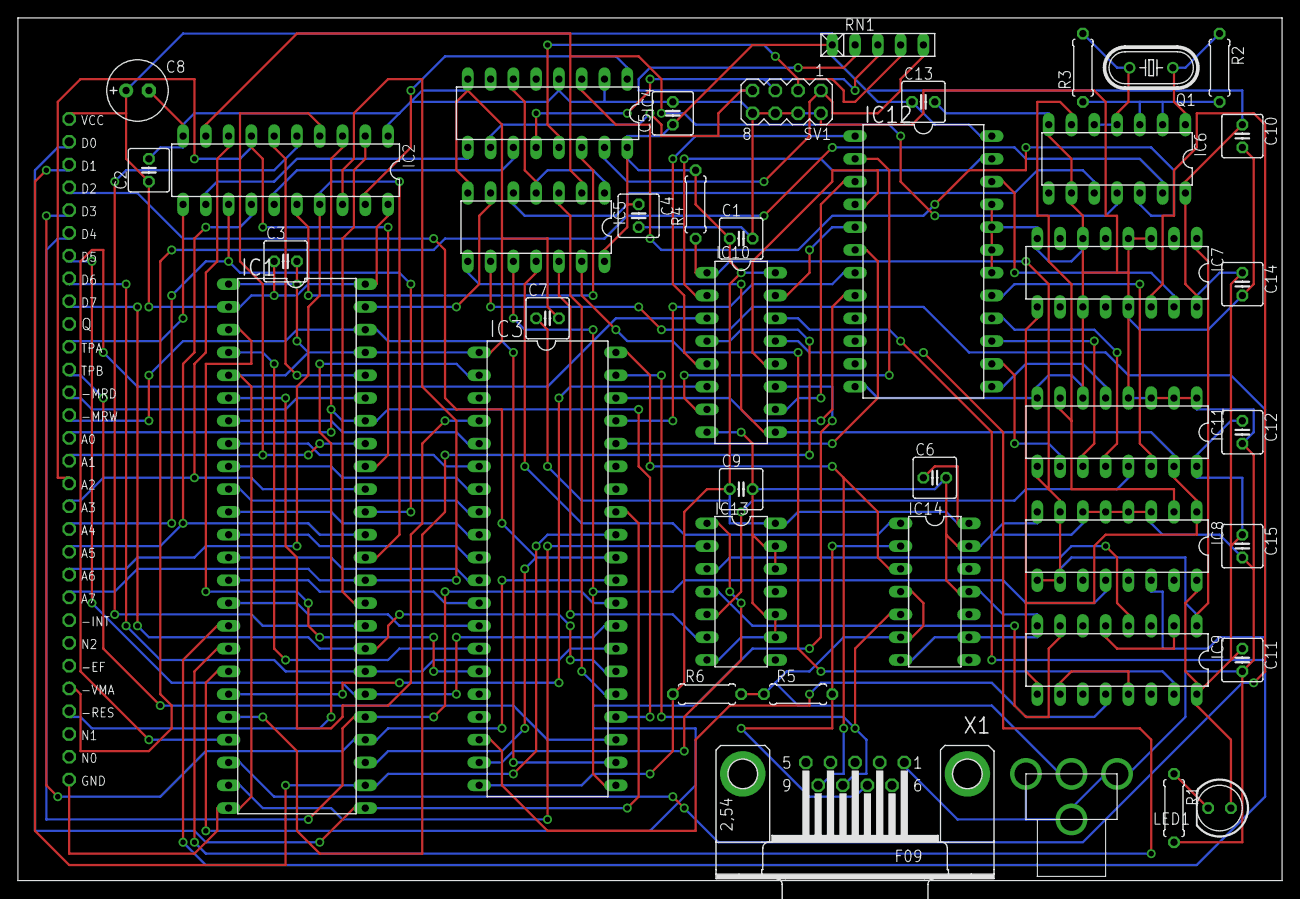
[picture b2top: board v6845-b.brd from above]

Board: 2 copper layers, 140.9 x 96.2 mm, 42 parts (0 on the bottom side), 99 nets.
